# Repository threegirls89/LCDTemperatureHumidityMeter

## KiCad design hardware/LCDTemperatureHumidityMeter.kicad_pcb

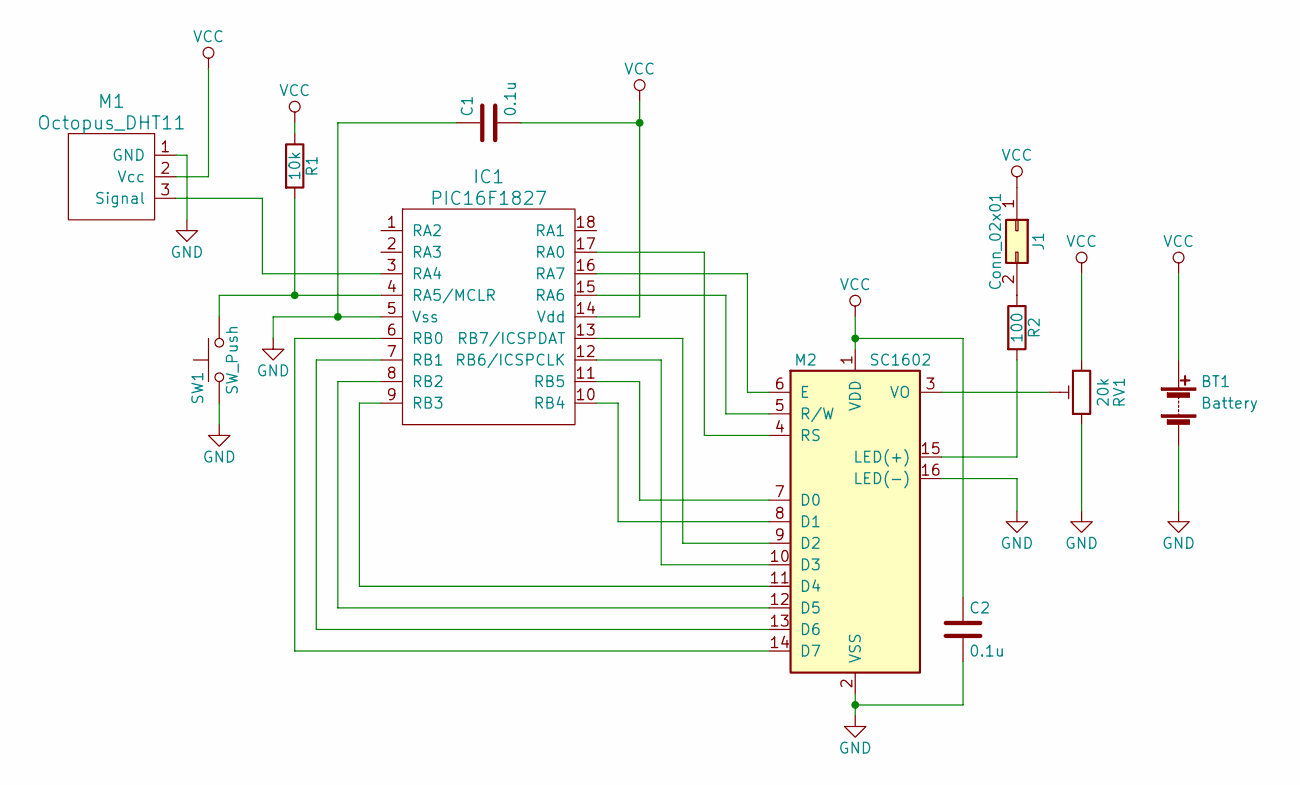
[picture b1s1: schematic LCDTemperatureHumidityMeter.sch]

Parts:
BT1: Battery; Pin_Header_Straight_1x02_Pitch2.54mm
C1, C2: 0.1u; C_0402
IC1: PIC16F1827; DIP-18_W7.62mm_Socket
J1: Conn_02x01; Pin_Header_Straight_1x02_Pitch2.54mm
M1: Octopus_DHT11; Pin_Header_Straight_1x03_Pitch2.54mm
M2: SC1602
R1: 10k; R_Axial_DIN0204_L3.6mm_D1.6mm_P5.08mm_Horizontal
R2: 100; R_Axial_DIN0204_L3.6mm_D1.6mm_P5.08mm_Horizontal
RV1: 20k; Potentiometer_Trimmer_Copal_CT-6EP
SW1: SW_Push; SW_Tactile_Straight_KSL0Axx1LFTR

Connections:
GND: BT1.2 (-), C1.1, C2.2, IC1.5 (Vss), M1.1 (GND), M2.2 (VSS), M2.16 (LED(-)), RV1.1, SW1.2
unnamed: IC1.3 (RA4), M1.3 (Signal)
unnamed: IC1.4 (RA5/MCLR), R1.2, SW1.1
unnamed: IC1.6 (RB0), M2.14 (D7)
unnamed: IC1.7 (RB1), M2.13 (D6)
unnamed: IC1.8 (RB2), M2.12 (D5)
unnamed: IC1.9 (RB3), M2.11 (D4)
unnamed: IC1.10 (RB4), M2.8 (D1)
unnamed: IC1.11 (RB5), M2.7 (D0)
unnamed: IC1.12 (RB6/ICSPCLK), M2.10 (D3)
unnamed: IC1.13 (RB7/ICSPDAT), M2.9 (D2)
unnamed: IC1.15 (RA6), M2.5 (R/W)
unnamed: IC1.16 (RA7), M2.6 (E)
unnamed: IC1.17 (RA0), M2.4 (RS)
unnamed: J1.2, R2.1
unnamed: M2.3 (VO), RV1.2
unnamed: M2.15 (LED(+)), R2.2
VCC: BT1.1 (+), C1.2, C2.1, IC1.14 (Vdd), J1.1, M1.2 (Vcc), M2.1 (VDD), R1.1, RV1.3

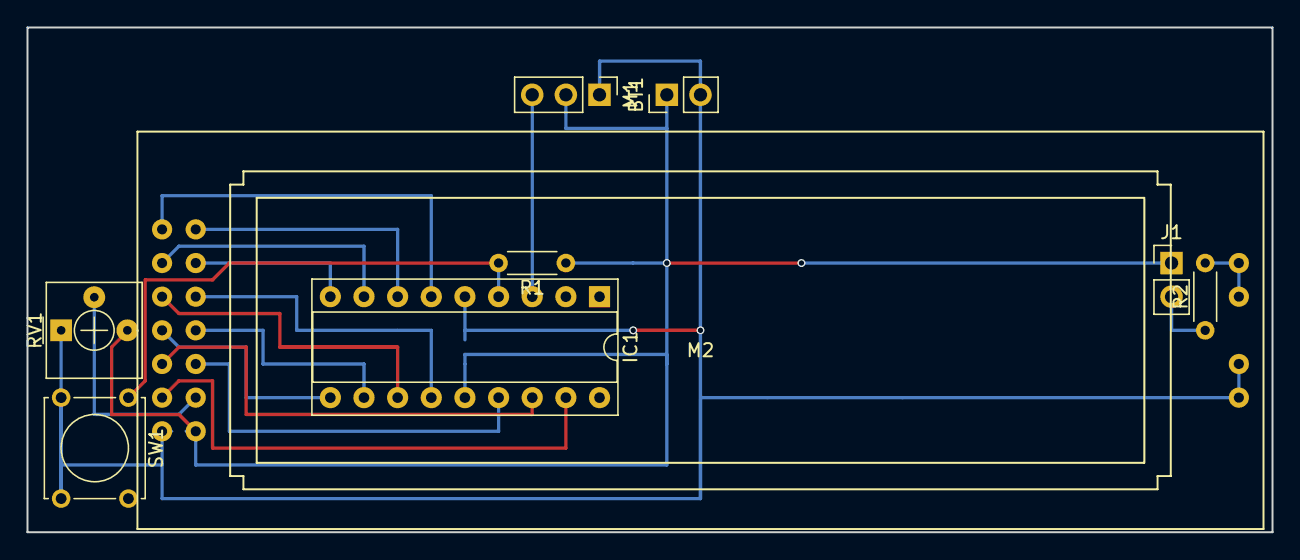
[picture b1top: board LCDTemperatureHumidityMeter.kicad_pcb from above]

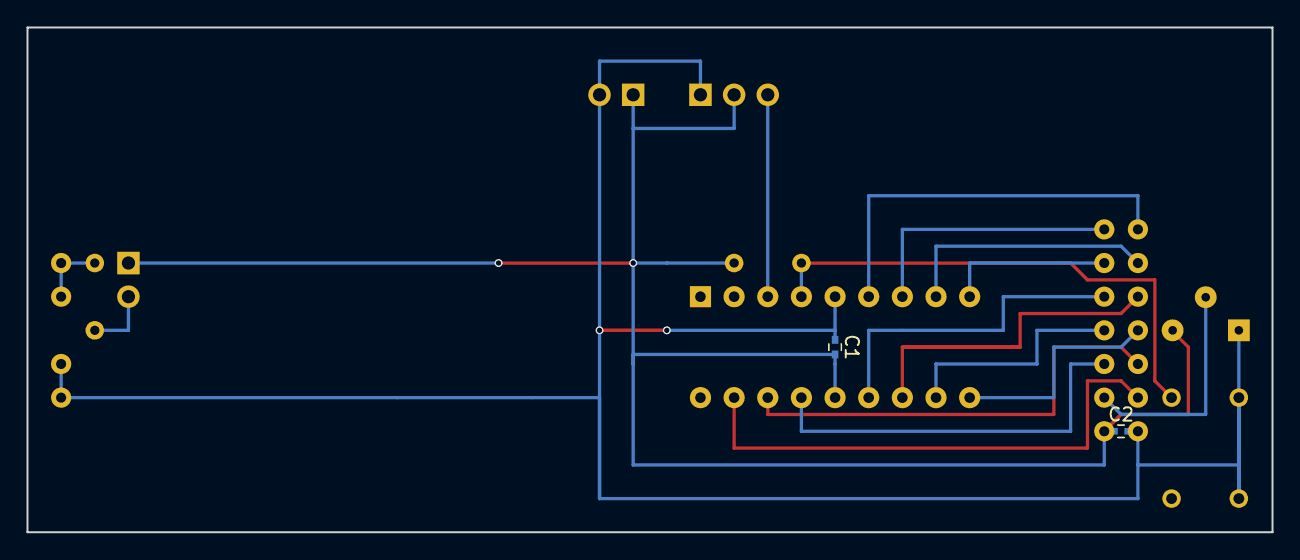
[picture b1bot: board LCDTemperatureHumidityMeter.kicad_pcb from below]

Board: 2 copper layers, 94.0 x 38.1 mm, 11 parts (2 on the bottom side), 18 nets.

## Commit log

2018-03-16 回路図実体配線図初版
2018-03-24 基板設計完了と，それに伴い配線の変更。
2018-04-18 picのプログラムを追加
